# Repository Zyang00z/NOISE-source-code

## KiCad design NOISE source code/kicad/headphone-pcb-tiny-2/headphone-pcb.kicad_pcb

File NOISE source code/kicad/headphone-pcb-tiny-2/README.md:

# Kidcad files for the PCB design of the headphone

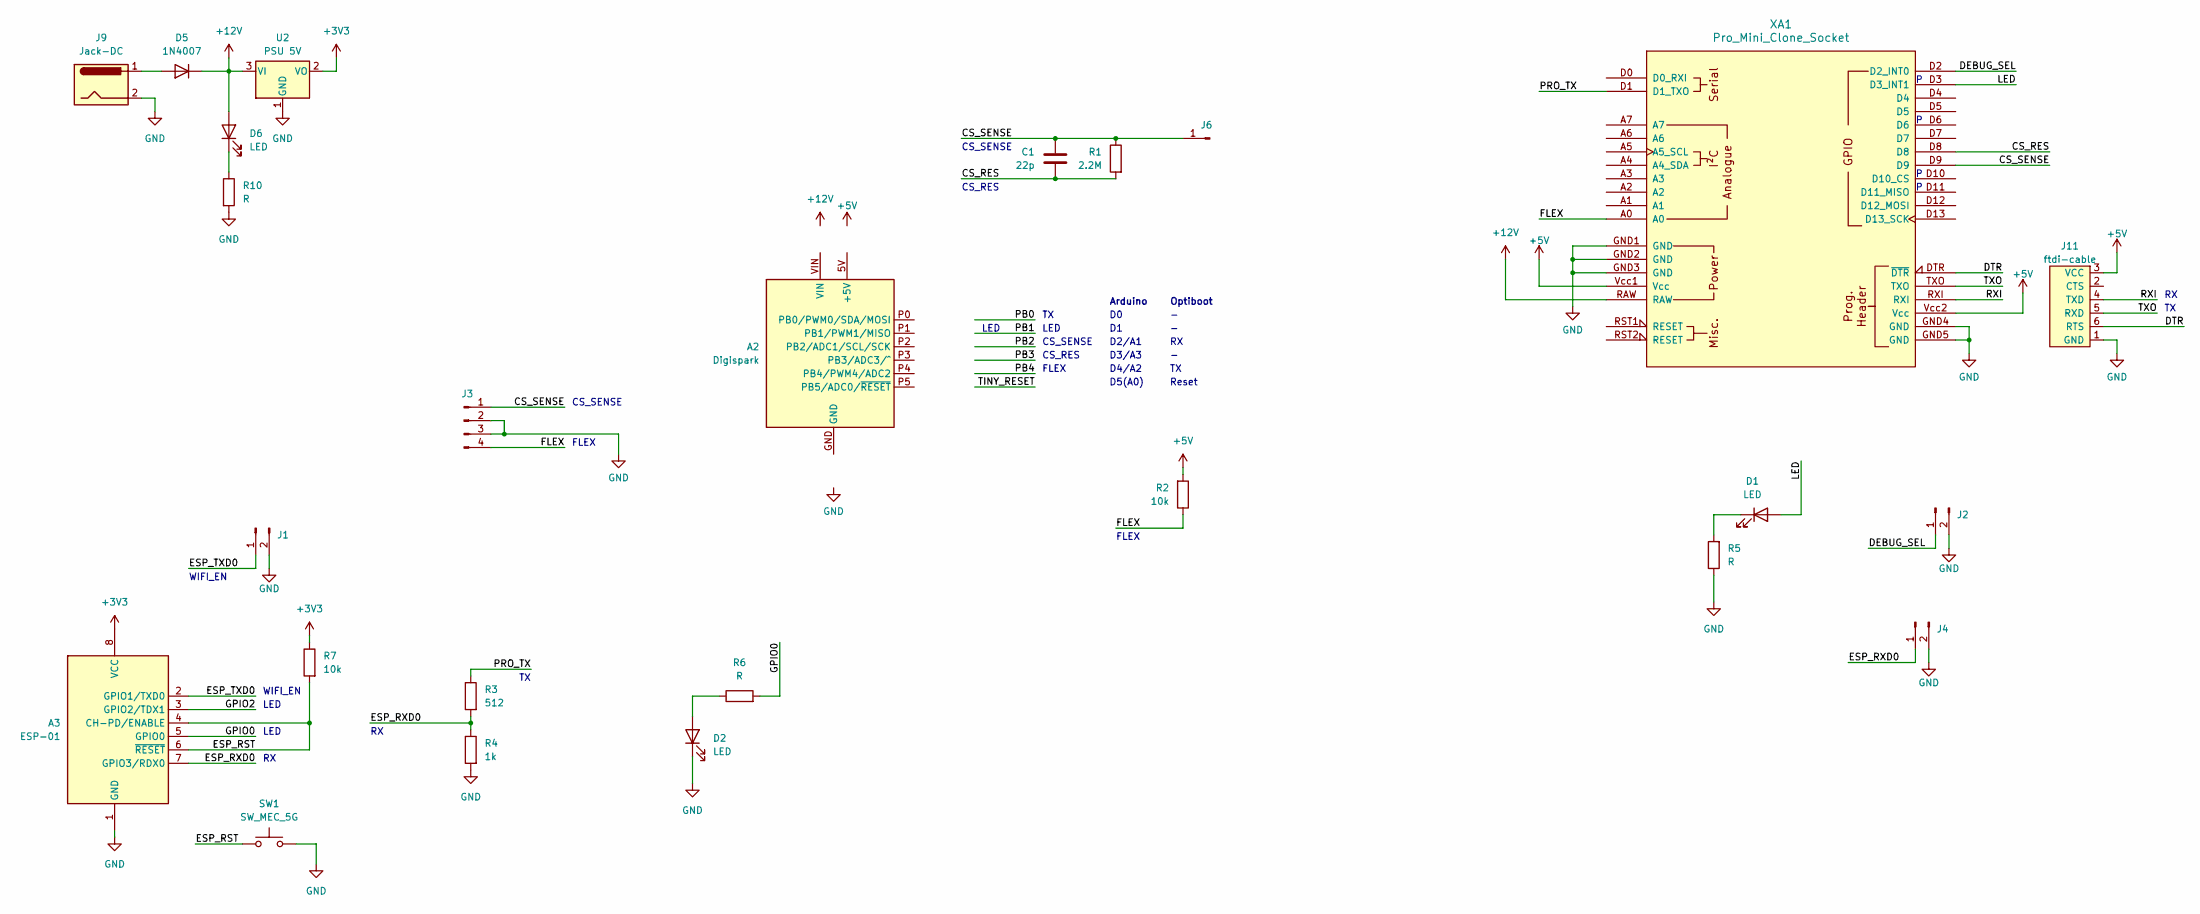
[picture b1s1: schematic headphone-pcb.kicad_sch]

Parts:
A2: Digispark
A3: ESP-01
C1: 22p; C_Rect_L7.0mm_W2.5mm_P5.00mm
D1, D2, D6: LED; LED_D3.0mm_Clear
D5: 1N4007; D_DO-41_SOD81_P10.16mm_Horizontal
J1, J2, J4: Conn_01x02_Pin; PinHeader_1x02_P2.54mm_Vertical
J3: Conn_01x04_Pin; PinHeader_1x04_P2.54mm_Horizontal
J6: Conn_01x01_Pin; Stud
J9: Jack-DC; DC_Power_Jack_PCB_Mounted_2.1mm
J11: ftdi-cable
R1: 2.2M; Resistor_TH_Vertical
R2, R7: 10k; Resistor_THT
R3: 512; Resistor_THT
R4: 1k; Resistor_THT
R5, R6, R10: R; Resistor_THT
SW1: SW_MEC_5G; Sw_Tact_PCB
U2: PSU 5V; dsun
XA1: Pro_Mini_Clone_Socket; Arduino_Pro_Mini_Socket

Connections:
+3V3: A3.8 (VCC), R7.1, U2.2 (VO)
+5V: J11.3 (VCC), R2.2, XA1.Vcc1 (Vcc), XA1.Vcc2 (Vcc)
+12V: D5.1 (K), D6.2 (A), U2.3 (VI), XA1.RAW
/CS_RES: C1.2, R1.2, XA1.D8
/CS_SENSE: C1.1, J3.1, J6.1, R1.1, XA1.D9
/DEBUG_SEL: J2.1, XA1.D2 (D2_INT0)
/DTR: J11.6 (RTS), XA1.DTR (~DTR)
/ESP_RST: A3.4 (CH-PD/ENABLE), A3.6 (~RESET), R7.2, SW1.1
/ESP_RXD0: A3.7 (GPIO3/RDX0), J4.1, R3.2, R4.1
/ESP_TXD0: A3.2 (GPIO1/TXD0), J1.1
/FLEX: J3.4, R2.1, XA1.A0
/GPIO0: A3.5 (GPIO0), R6.2
/GPIO2: A3.3 (GPIO2/TDX1)
/LED: D1.2 (A), XA1.D3 (D3_INT1)
/PRO_TX: R3.1, XA1.D1 (D1_TXO)
/RXI: J11.4 (TXD), XA1.RXI
/TXO: J11.5 (RXD), XA1.TXO
GND: A3.1 (GND), D2.1 (K), J1.2, J2.2, J3.2, J3.3, J4.2, J9.2, J11.1 (GND), R4.2, R5.1, R10.2, SW1.2, U2.1 (GND), XA1.GND1 (GND), XA1.GND2 (GND), XA1.GND3 (GND), XA1.GND4 (GND), XA1.GND5 (GND)
unnamed: D1.1 (K), R5.2
unnamed: D2.2 (A), R6.1
unnamed: D5.2 (A), J9.1
unnamed: D6.1 (K), R10.1

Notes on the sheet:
CS_SENSE
CS_RES
LED
D5(A0)
D4/A2
D3/A3
D2/A1
FLEX
WIFI_EN
Arduino
Reset
Optiboot

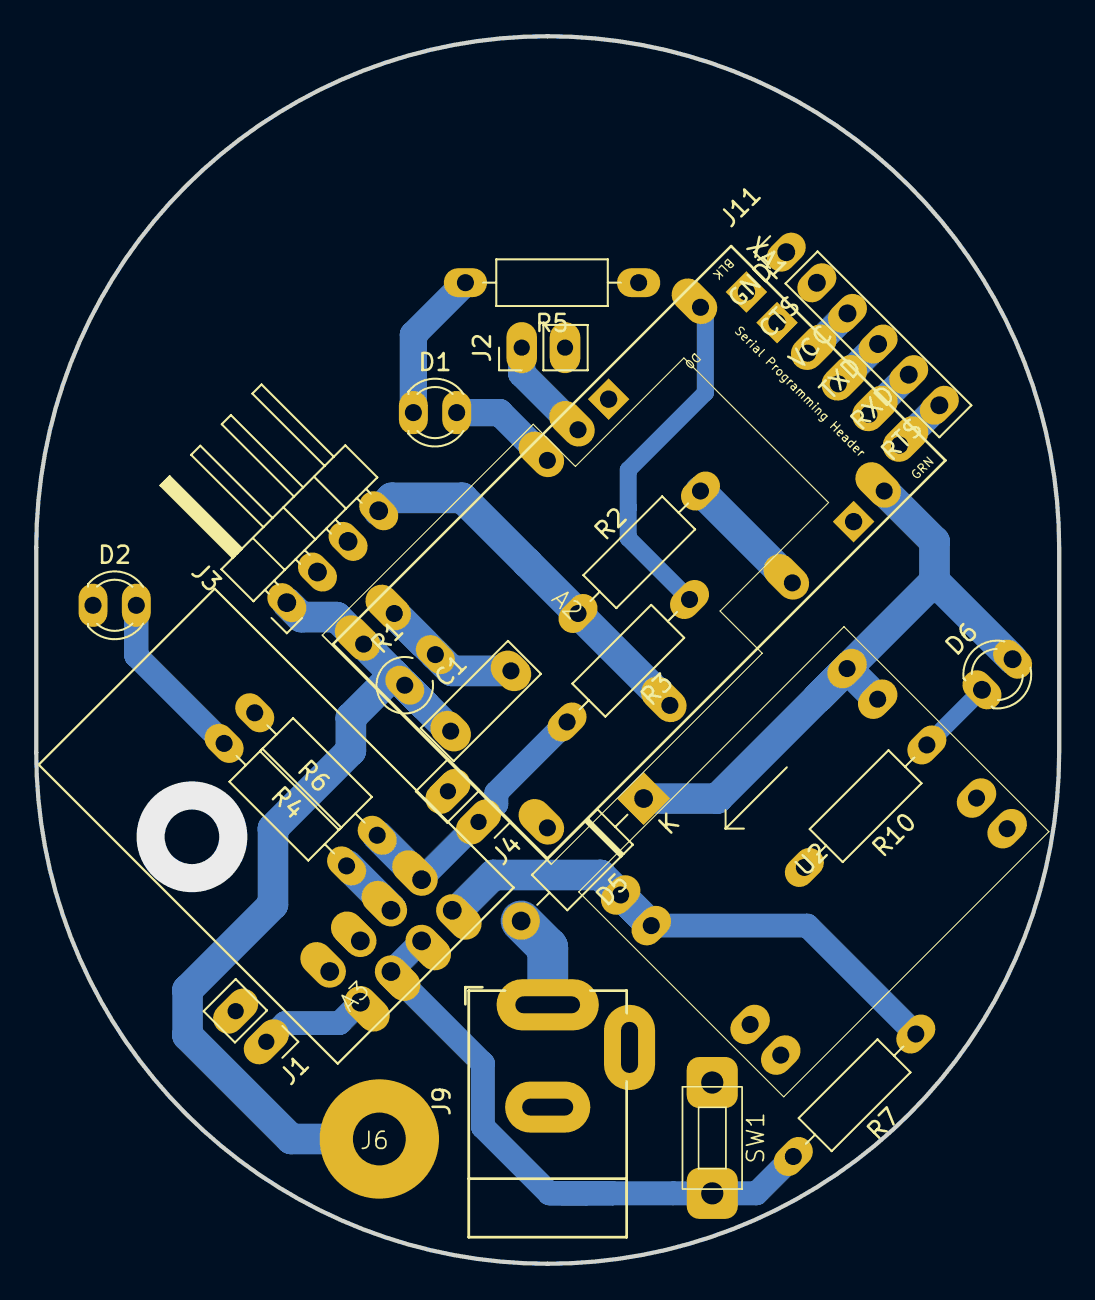
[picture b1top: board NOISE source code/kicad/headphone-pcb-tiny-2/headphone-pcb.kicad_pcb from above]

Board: 2 copper layers, 60.0 x 72.0 mm, 25 parts (0 on the bottom side), 21 nets.

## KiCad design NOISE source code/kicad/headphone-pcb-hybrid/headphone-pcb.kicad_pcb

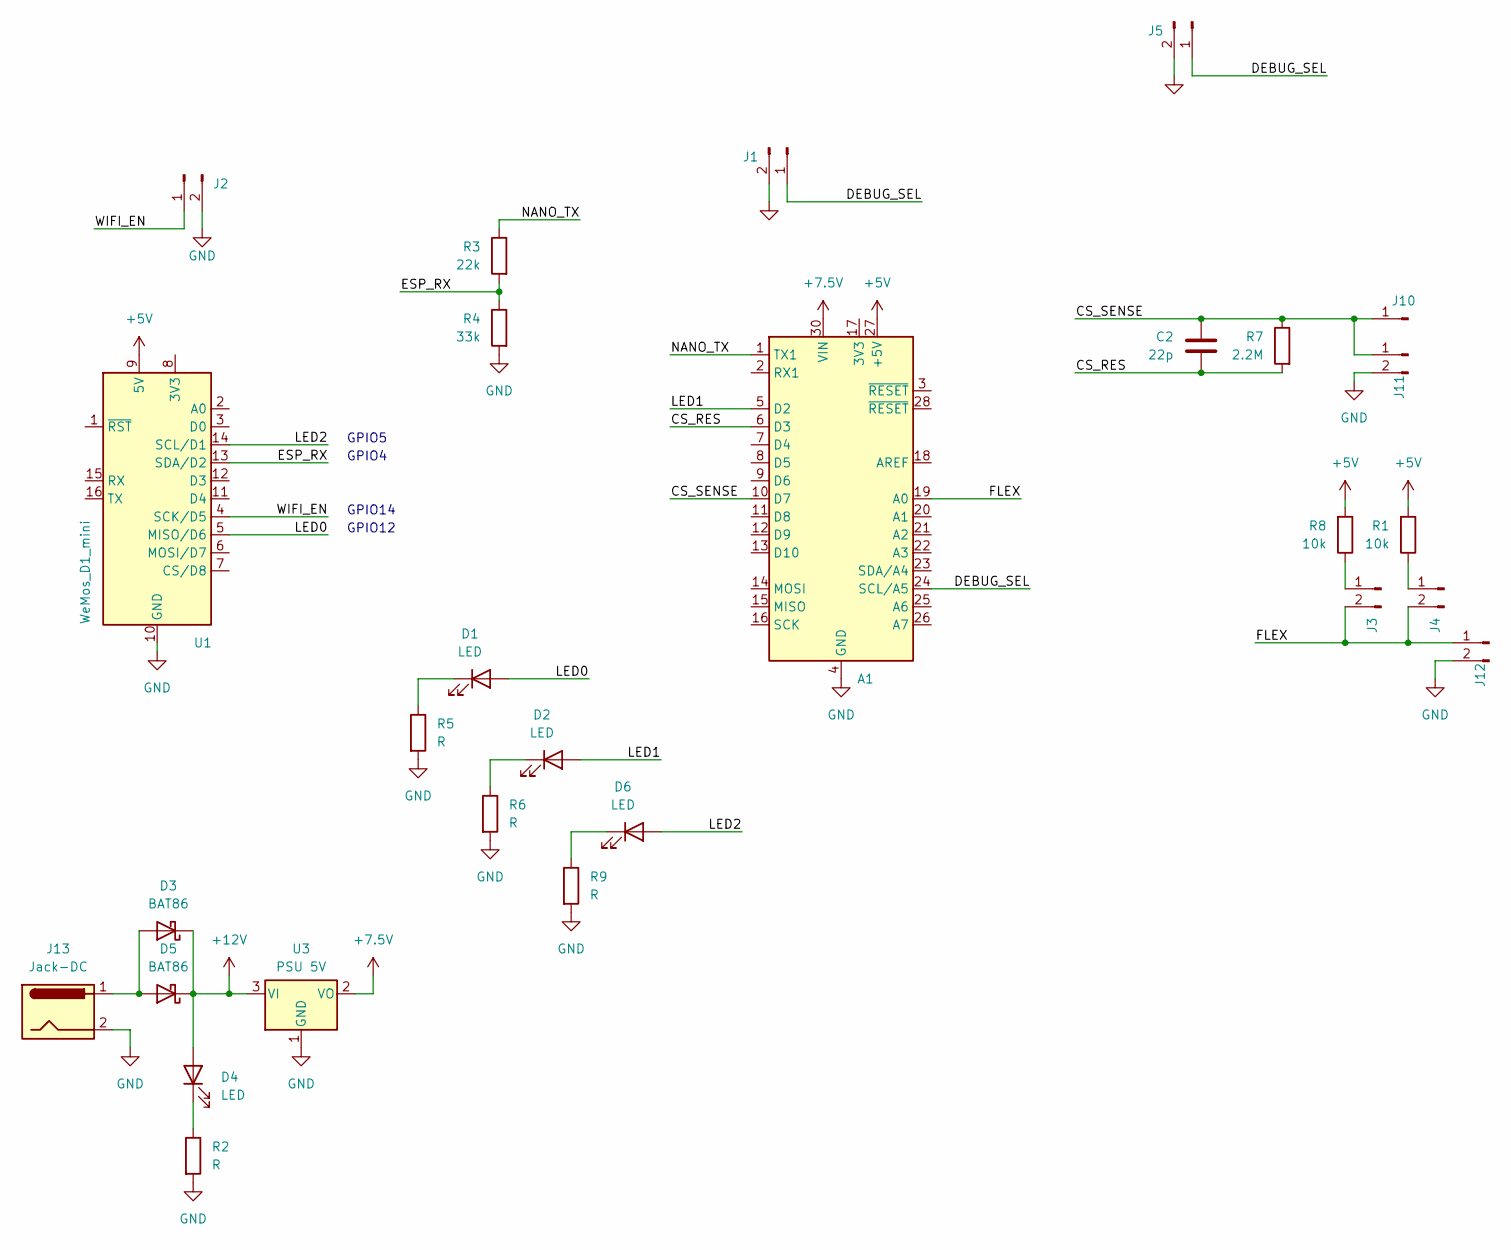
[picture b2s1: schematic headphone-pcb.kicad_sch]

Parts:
A1: Arduino_Nano_Every; Arduino_Nano
C2: 22p; C_Disc_D6.0mm_W2.5mm_P5.00mm
D1, D2: LED; LED_D5.0mm_Clear
D3, D5: BAT86; D_DO-34_SOD68_P7.62mm_Horizontal
D4, D6: LED; LED_D3.0mm_Clear
J1, J2, J3, J4, J5, J11, J12: Conn_01x02_Pin; PinHeader_1x02_P2.54mm_Vertical
J10: Conn_01x01_Pin; Stud
J13: Jack-DC; DC_Power_Jack_PCB_Mounted_2.1mm
R1, R8: 10k; R_Axial_DIN0207_L6.3mm_D2.5mm_P10.16mm_Horizontal
R2, R5, R6, R9: R; R_Axial_DIN0207_L6.3mm_D2.5mm_P10.16mm_Horizontal
R3: 22k; R_Axial_DIN0207_L6.3mm_D2.5mm_P10.16mm_Horizontal
R4: 33k; R_Axial_DIN0207_L6.3mm_D2.5mm_P10.16mm_Horizontal
R7: 2.2M; R_Axial_DIN0207_L6.3mm_D2.5mm_P10.16mm_Horizontal
U1: WeMos_D1_mini; WEMOS_D1_mini_light
U3: PSU 5V; dsun

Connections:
+5V: A1.27 (+5V), R1.2, R8.2, U1.9 (5V)
+7.5V: A1.30 (VIN), U3.2 (VO)
+12V: D3.1 (K), D4.2 (A), D5.1 (K), U3.3 (VI)
/CS_RES: A1.10 (D7), C2.1, J10.1, J11.1, R7.1
/CS_SENSE: A1.6 (D3), C2.2, R7.2
/DEBUG_SEL: A1.24 (SCL/A5), J1.1, J5.1
/ESP_RX: R3.2, R4.1, U1.13 (SDA/D2)
/FLEX: A1.19 (A0), J3.2, J4.2, J12.1
/LED0: D1.2 (A), U1.5 (MISO/D6)
/LED1: A1.5 (D2), D2.2 (A)
/LED2: D6.2 (A), U1.14 (SCL/D1)
/NANO_TX: A1.1 (TX1), R3.1
/WIFI_EN: J2.1, U1.4 (SCK/D5)
GND: A1.4 (GND), A1.29 (GND), J1.2, J2.2, J5.2, J11.2, J12.2, J13.2, R2.2, R4.2, R5.2, R6.2, R9.2, U1.10 (GND), U3.1 (GND)
unnamed: D1.1 (K), R5.1
unnamed: D2.1 (K), R6.1
unnamed: D3.2 (A), D5.2 (A), J13.1
unnamed: D4.1 (K), R2.1
unnamed: D6.1 (K), R9.1
unnamed: J3.1, R8.1
unnamed: J4.1, R1.1

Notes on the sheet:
GPIO4
GPIO14
GPIO12
GPIO5

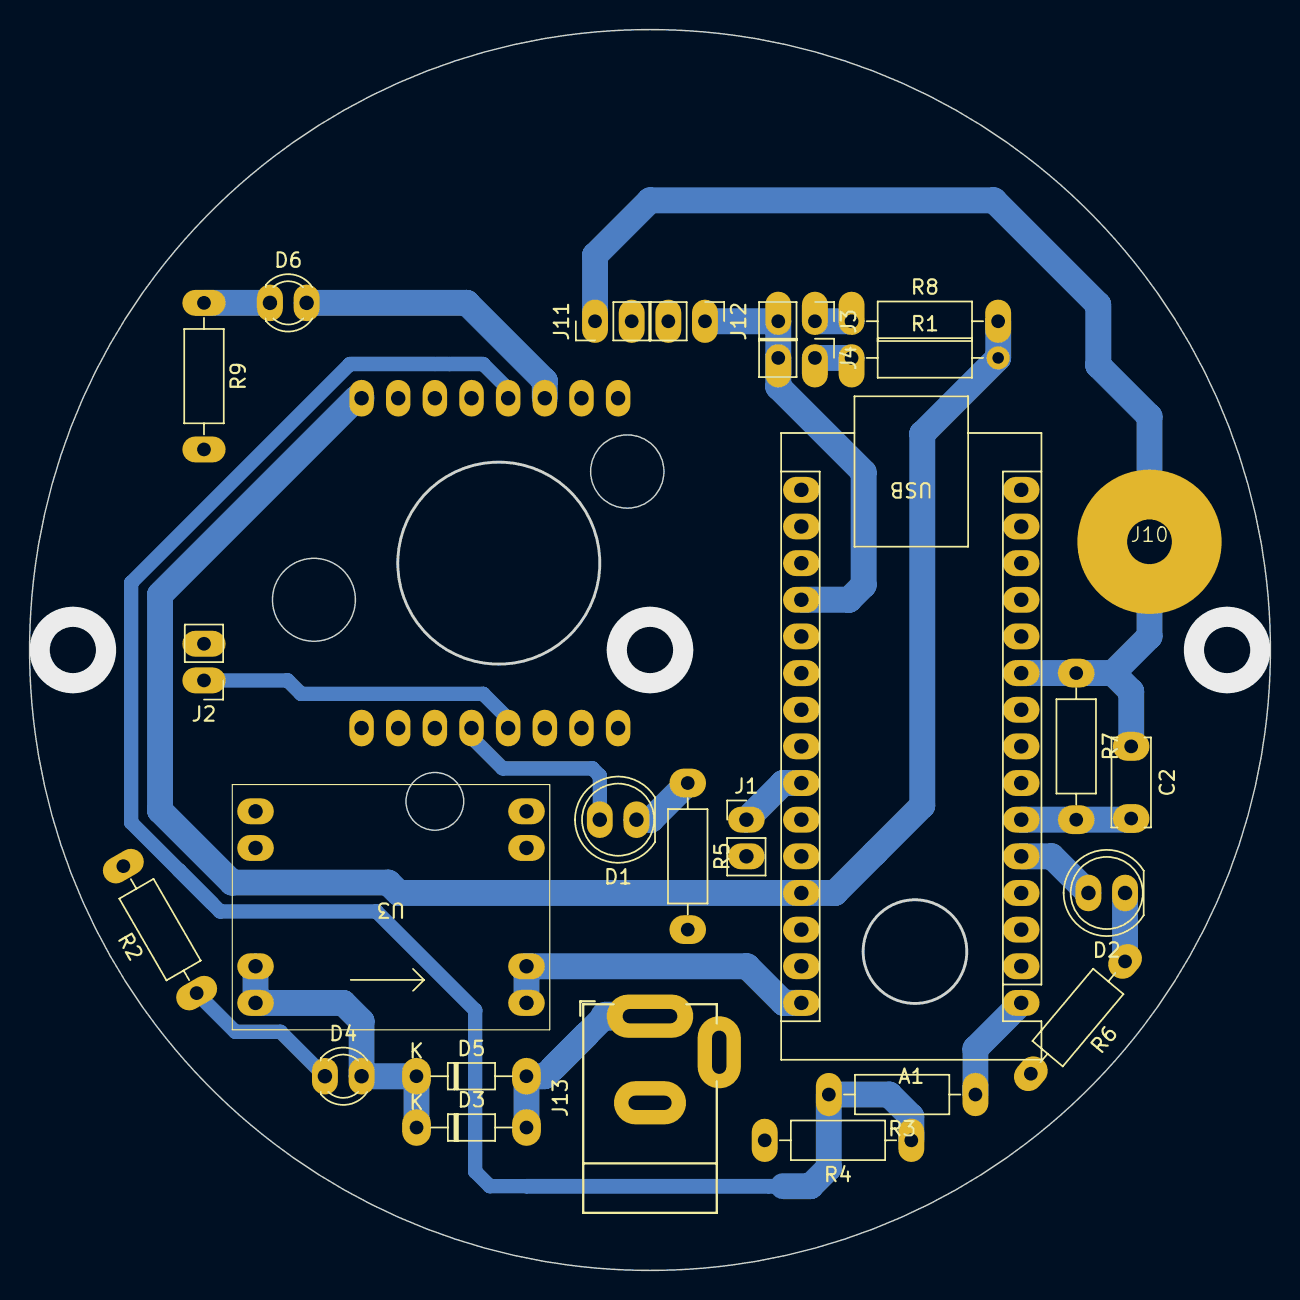
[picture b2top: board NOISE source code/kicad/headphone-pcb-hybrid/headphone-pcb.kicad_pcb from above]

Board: 2 copper layers, 85.9 x 85.9 mm, 27 parts (1 on the bottom side), 21 nets.
